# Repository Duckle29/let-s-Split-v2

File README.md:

# This repo is now an archive. Further boards and development can be found here: https://github.com/Duckle29/Vitamins-included

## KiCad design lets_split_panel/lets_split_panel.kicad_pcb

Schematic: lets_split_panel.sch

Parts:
FID1, FID2, FID3, FID4, FID5, FID6: Fiducial; Fiducial_1mm_Dia_2mm_Outer

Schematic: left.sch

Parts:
C1, C4: 1uF; C_0603
C2, C3: 18pF; C_0603
D1, D2, D3, D4, D5, D6, D7, D8, D9, D10, D11, D12: BAV70; SOT-23
J1: Speaker; Buzzer_12x9.5RM7.6
J3: ISP; Pin_Header_Straight_2x03_Pitch2.54mm
J7: WS2812>; Pin_Header_Straight_1x01_Pitch2.54mm
JP1, JP2: I2C pullup; Solder-jumper-NO
P2: UJ2-MBH-1-SMT; USB-Mini-B-SMD
P3: >WS2812; SMD_PAD_1x03_Pitch2.54mm
P4: SJ-43514-SMT; SJ-4351X-SMT
R1, R2, R6: 4k7; R_0603
R3: 200R; R_0603
R4, R5: 22R; R_0603
SW1, SW2, SW3, SW4, SW5, SW6, SW7, SW8, SW9, SW10, SW11, SW12, SW13, SW14, SW15, SW16, SW17, SW18, SW19, SW20, SW21, SW22, SW23, SW24: Socket; Kailh-socket
U1: ATMega32U4; QFN44G-0.5-7X7MM
Y1: 16MHz; Crystal_SMD_Abracon_ABM3-2pin_5.0x3.2mm

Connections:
/Left half/D+: R5.2, U1.4 (D+)
/Left half/D-: R4.2, U1.3 (D-)
/Left half/Dd+: P2.3 (D+), R5.1
/Left half/Dd-: P2.2 (D-), R4.1
/Left half/MISO: J3.1, U1.11 ((MISO)PB3)
/Left half/MOSI: J3.4, U1.10 ((MOSI)PB2)
/Left half/SCK: J3.3, U1.9 ((SCK)PB1)
/Left half/SCL/D3: P4.3, R2.2, U1.18 (~~(INT0/SCL)PD0)
/Left half/SDA: J7.1, P4.4, R1.2, U1.19 ((INT1/SDA)PD1)
/Left half/buzz: R3.1, U1.31 (~~PC6)
/Left half/col0: SW1.1, SW7.1, SW13.1, SW19.1, U1.40 ((A1)PF1)
/Left half/col1: SW2.2, SW8.2, SW14.2, SW20.2, U1.39 ((A4)PF4)
/Left half/col2: SW3.1, SW9.1, SW15.1, SW21.1, U1.33 (PE2)
/Left half/col3: SW4.2, SW10.2, SW16.2, SW22.2, U1.30 (~~(A13)PB6)
/Left half/col4: SW5.1, SW11.1, SW17.1, SW23.1, U1.27 (~~(ADC10)PD7)
/Left half/col5: SW6.2, SW12.2, SW18.2, SW24.2, U1.26 (~~(ADC9)PD6); also elsewhere on the board
/Left half/row0: D1.3, D2.3, D3.3, U1.38 ((A5)PF5)
/Left half/row1: D4.3, D5.3, D6.3, U1.37 ((A6)PF6)
/Left half/row2: D7.3, D8.3, D9.3, U1.32 (~~PC7)
/Left half/row3: D10.3, D11.3, D12.3, U1.36 ((A7)PF7)
/Left half/wd2812-in: P3.2, U1.41 ((A0)PF0)
/Left half/~Reset: J3.5, R6.1, U1.13 (~RESET~)
GND: C1.2, C2.2, C3.2, C4.2, J1.2, J3.6, P2.5 (GND), P2.6 (shield), P3.3, P4.1, U1.5 (UGND), U1.15 (GND), U1.23 (GND), U1.35 (GND), U1.43 (GND), U1.TAB (GND); also elsewhere on the board
unnamed: C2.1, U1.17 (XTAL1), Y1.1
unnamed: C3.1, U1.16 (XTAL2), Y1.2
unnamed: C4.1, U1.6 (UCap)
unnamed: D1.1, SW1.2
unnamed: D1.2, SW2.1
unnamed: D2.1, SW3.2
unnamed: D2.2, SW4.1
unnamed: D3.1, SW5.2
unnamed: D3.2, SW6.1
unnamed: D4.1, SW7.2
unnamed: D4.2, SW8.1
unnamed: D5.1, SW9.2
unnamed: D5.2, SW10.1
unnamed: D6.1, SW11.2
unnamed: D6.2, SW12.1
unnamed: D7.1, SW13.2
unnamed: D7.2, SW14.1
unnamed: D8.1, SW15.2
unnamed: D8.2, SW16.1
unnamed: D9.1, SW17.2
unnamed: D9.2, SW18.1
unnamed: D10.1, SW19.2
unnamed: D10.2, SW20.1
unnamed: D11.1, SW21.2
unnamed: D11.2, SW22.1
unnamed: D12.1, SW23.2
unnamed 74: D12.2, SW24.1; also elsewhere on the board
unnamed: J1.1, R3.2
unnamed: JP1.2, R1.1
unnamed: JP2.2, R2.1
VBUS: C1.1, J3.2, JP1.1, JP2.1, P2.1 (VCC), P3.1, P4.2, R6.2, U1.2 (UVCC), U1.7 (VBUS), U1.14 (VCC), U1.24 (AVCC), U1.34 (VCC), U1.44 (AVCC); also elsewhere on the board

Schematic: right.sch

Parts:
C5, C8: 1uF; C_0603
C6, C7: 18pF; C_0603
D13, D14, D15, D16, D17, D18, D19, D20, D21, D22, D23, D24: BAV70; SOT-23
J5: Speaker; Buzzer_12x9.5RM7.6
J6: ISP; Pin_Header_Straight_2x03_Pitch2.54mm
J8: WS2812>; Pin_Header_Straight_1x01_Pitch2.54mm
P5: UJ2-MBH-1-SMT; USB-Mini-B-SMD
P6: >WS2812; SMD_PAD_1x03_Pitch2.54mm
P8: SJ-43514-SMT; SJ-4351X-SMT
R7, R8: 22R; R_0603
R9: 4k7; R_0603
R10: 200R; R_0603
SW25, SW26, SW27, SW28, SW29, SW30, SW31, SW32, SW33, SW34, SW35, SW36, SW37, SW38, SW39, SW40, SW41, SW42, SW43, SW44, SW45, SW46, SW47, SW48: Socket; Kailh-socket
U2: ATMega32U4; QFN44G-0.5-7X7MM
Y2: 16MHz; Crystal_SMD_Abracon_ABM3-2pin_5.0x3.2mm

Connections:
/Right half/D+: R8.2, U2.4 (D+)
/Right half/D-: R7.2, U2.3 (D-)
/Right half/Dd+: P5.3 (D+), R8.1
/Right half/Dd-: P5.2 (D-), R7.1
/Right half/MISO: J6.1, U2.11 ((MISO)PB3)
/Right half/MOSI: J6.4, U2.10 ((MOSI)PB2)
/Right half/SCK: J6.3, U2.9 ((SCK)PB1)
/Right half/SCL/D3: P8.3, U2.18 (~~(INT0/SCL)PD0)
/Right half/SDA: J8.1, P8.4, U2.19 ((INT1/SDA)PD1)
/Right half/WD2812-in: P6.2, U2.41 ((A0)PF0)
/Right half/buzz: R10.1, U2.31 (~~PC6)
/Right half/col0: SW25.1, SW31.1, SW37.1, SW43.1, U2.40 ((A1)PF1); also elsewhere on the board
/Right half/col1: SW26.2, SW32.2, SW38.2, SW44.2, U2.39 ((A4)PF4)
/Right half/col2: SW27.1, SW33.1, SW39.1, SW45.1, U2.33 (PE2)
/Right half/col3: SW28.2, SW34.2, SW40.2, SW46.2, U2.30 (~~(A13)PB6)
/Right half/col4: SW29.1, SW35.1, SW41.1, SW47.1, U2.27 (~~(ADC10)PD7)
/Right half/col5: SW30.2, SW36.2, SW42.2, SW48.2, U2.26 (~~(ADC9)PD6)
/Right half/row0: D13.3, D14.3, D15.3, U2.38 ((A5)PF5)
/Right half/row1: D16.3, D17.3, D18.3, U2.37 ((A6)PF6)
/Right half/row2: D19.3, D20.3, D21.3, U2.32 (~~PC7)
/Right half/row3: D22.3, D23.3, D24.3, U2.36 ((A7)PF7)
/Right half/~RESET: J6.5, R9.1, U2.13 (~RESET~)
GND: C5.2, C6.2, C7.2, C8.2, J5.2, J6.6, P5.5 (GND), P5.6 (shield), P6.3, P8.1, U2.5 (UGND), U2.15 (GND), U2.23 (GND), U2.35 (GND), U2.43 (GND), U2.TAB (GND); also elsewhere on the board
unnamed: C6.1, U2.17 (XTAL1), Y2.1
unnamed: C7.1, U2.16 (XTAL2), Y2.2
unnamed: C8.1, U2.6 (UCap)
unnamed: D13.1, SW25.2
unnamed: D13.2, SW26.1
unnamed: D14.1, SW27.2
unnamed: D14.2, SW28.1
unnamed: D15.1, SW29.2
unnamed: D15.2, SW30.1
unnamed: D16.1, SW31.2
unnamed: D16.2, SW32.1
unnamed: D17.1, SW33.2
unnamed: D17.2, SW34.1
unnamed: D18.1, SW35.2
unnamed: D18.2, SW36.1
unnamed: D19.1, SW37.2
unnamed: D19.2, SW38.1
unnamed: D20.1, SW39.2
unnamed: D20.2, SW40.1
unnamed: D21.1, SW41.2
unnamed: D21.2, SW42.1
unnamed 93: D22.1, SW43.2; also elsewhere on the board
unnamed: D22.2, SW44.1
unnamed: D23.1, SW45.2
unnamed: D23.2, SW46.1
unnamed: D24.1, SW47.2
unnamed: D24.2, SW48.1
unnamed: J5.1, R10.2
VBUS: C5.1, J6.2, P5.1 (VCC), P6.1, P8.2, R9.2, U2.2 (UVCC), U2.7 (VBUS), U2.14 (VCC), U2.24 (AVCC), U2.34 (VCC), U2.44 (AVCC); also elsewhere on the board

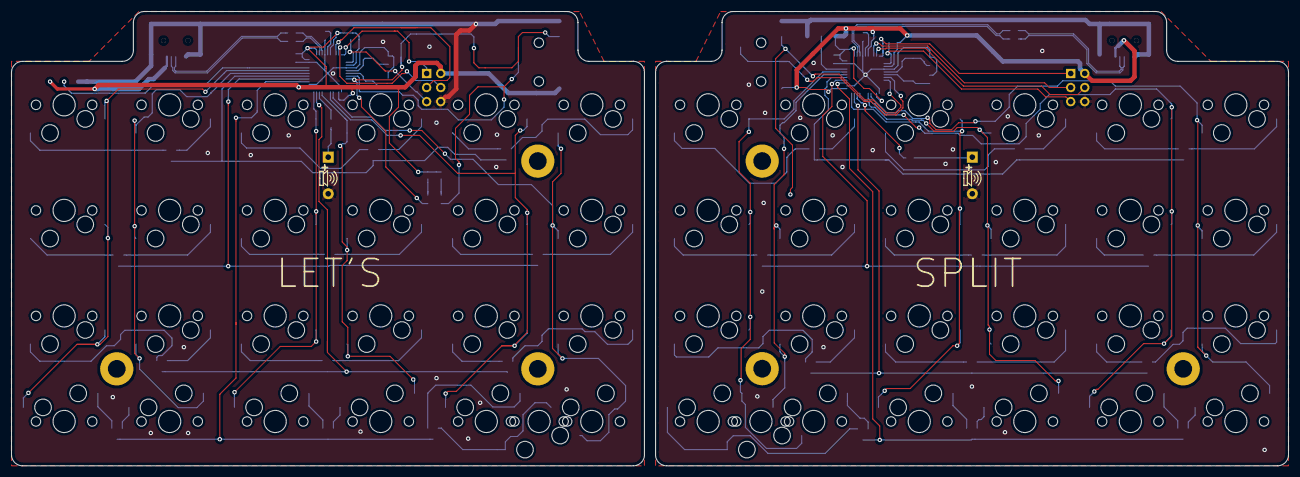
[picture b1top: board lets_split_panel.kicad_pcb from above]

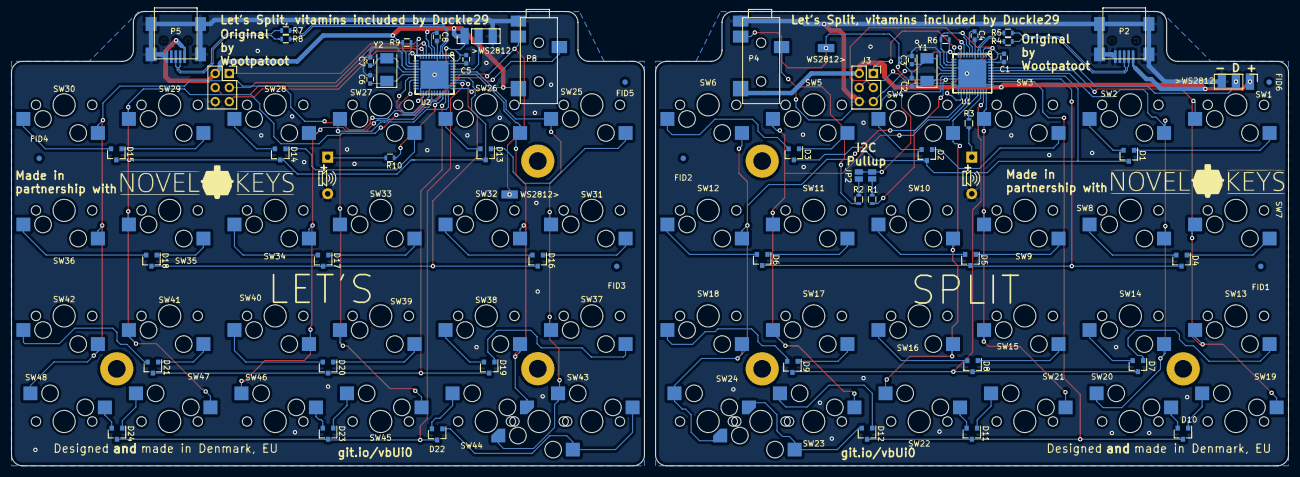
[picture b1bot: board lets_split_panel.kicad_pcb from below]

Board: 2 copper layers, 230.5 x 82.0 mm, 116 parts (64 on the bottom side), 104 nets.

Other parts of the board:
SW24#2, SW43#2: Socket; Kailh-socket

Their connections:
/Left half/col5: SW24#2.2; also elsewhere on the board
/Right half/col0: SW43#2.1; also elsewhere on the board
unnamed 74: SW24#2.1; also elsewhere on the board
unnamed 93: SW43#2.2; also elsewhere on the board

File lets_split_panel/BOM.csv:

"Id";"Designator";"Package";"Quantity";"Designation";"Supplier and ref";
1;"G***,G***";"kiwi";2;"LOGO";;;
2;"FID6,FID4,FID5,FID3,FID2,FID1";"Fiducial_1mm_Dia_2mm_Outer";6;"Fiducial";;;
3;"P5,P2";"USB-Mini-B-SMD";2;"UJ2-MBH-1-SMT";;;
4;"D21,D16,D23,D14,D20,D22,D19,D24,D17,D15,D13,D18,D2,D8,D6,D12,D3,D7,D10,D4,D9,D11,D5,D1";"SOT-23";24;"BAV70";;;
5;"R7,R8,R5,R4";"R_0603";4;"22R";;;
6;"SW40,SW36,SW41,SW43,SW44,SW42,SW45,SW43,SW35,SW28,SW34,SW48,SW47,SW33,SW39,SW32,SW26,SW29,SW46,SW30,SW38,SW27,SW31,SW25,SW37,SW19,SW12,SW21,SW23,SW24,SW24,SW6,SW15,SW4,SW5,SW13,SW20,SW1,SW22,SW16,SW17,SW8,SW10,SW11,SW7,SW9,SW18,SW2,SW14,SW3";"Kailh-socket";50;"Socket";;;
7;"Y2,Y1";"Crystal_SMD_Abracon_ABM3-2pin_5.0x3.2mm";2;"16MHz";;;
8;"P6,P3";"SMD_PAD_1x03_Pitch2.54mm";2;">WS2812";;;
9;"P8,P4";"SJ-4351X-SMT";2;"SJ-43514-SMT";;;
10;"J8,J7";"Pin_Header_Straight_1x01_Pitch2.54mm";2;"WS2812>";;;
11;"C6,C7,C2,C3";"C_0603";4;"18pF";;;
12;"C5,C8,C1,C4";"C_0603";4;"1uF";;;
13;"REF**,REF**,REF**,REF**,REF**,REF**";"1pin";6;"1pin";;;
14;"U2,U1";"QFN44G-0.5-7X7MM";2;"ATMega32U4";;;
15;"R10,R3";"R_0603";2;"200R";;;
16;"R9,R1,R2,R6";"R_0603";4;"4k7";;;
17;"J6,J3";"Pin_Header_Straight_2x03_Pitch2.54mm";2;"ISP";;;
18;"J5,J1";"Buzzer_12x9.5RM7.6";2;"Speaker";;;
19;"G***,G***";"NovelKeys";2;"LOGO";;;
20;"JP1,JP2";"Solder-jumper-NO";2;"I2C pullup";;;

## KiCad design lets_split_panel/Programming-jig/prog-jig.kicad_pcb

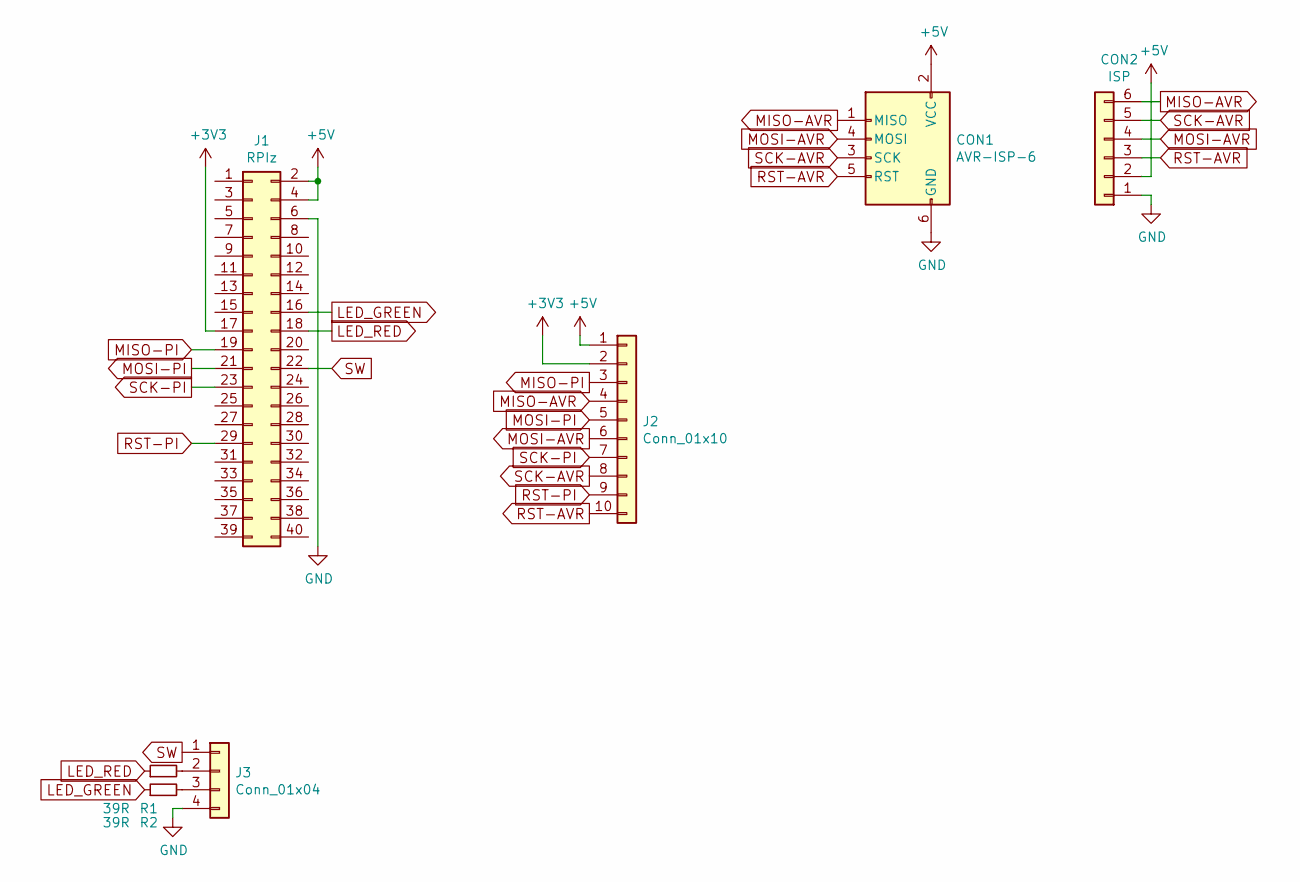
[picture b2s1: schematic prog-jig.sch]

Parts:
CON1: AVR-ISP-6; Pin_Header_Straight_2x03_Pitch2.54mm
CON2: ISP; Pin_Header_Straight_1x06_Pitch2.54mm
J1: RPIz; Socket_Strip_Straight_2x20_Pitch2.54mm
J2: Conn_01x10; Pin_Header_Straight_1x10_Pitch2.54mm
J3: Conn_01x04; Pin_Header_Angled_1x04_Pitch2.54mm
R1, R2: 39R; R_0603_HandSoldering

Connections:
+3V3: J1.17, J2.2
+5V: CON1.2 (VCC), CON2.2, J1.2, J1.4, J2.1
GND: CON1.6 (GND), CON2.1, J1.6, J3.4
LED_GREEN: J1.16, R2.1
LED_RED: J1.18, R1.1
MISO-AVR: CON1.1 (MISO), CON2.6, J2.4
MISO-PI: J1.19, J2.3
MOSI-AVR: CON1.4 (MOSI), CON2.4, J2.6
MOSI-PI: J1.21, J2.5
unnamed: J3.2, R1.2
unnamed: J3.3, R2.2
RST-AVR: CON1.5 (RST), CON2.3, J2.10
RST-PI: J1.29, J2.9
SCK-AVR: CON1.3 (SCK), CON2.5, J2.8
SCK-PI: J1.23, J2.7
SW: J1.22, J3.1

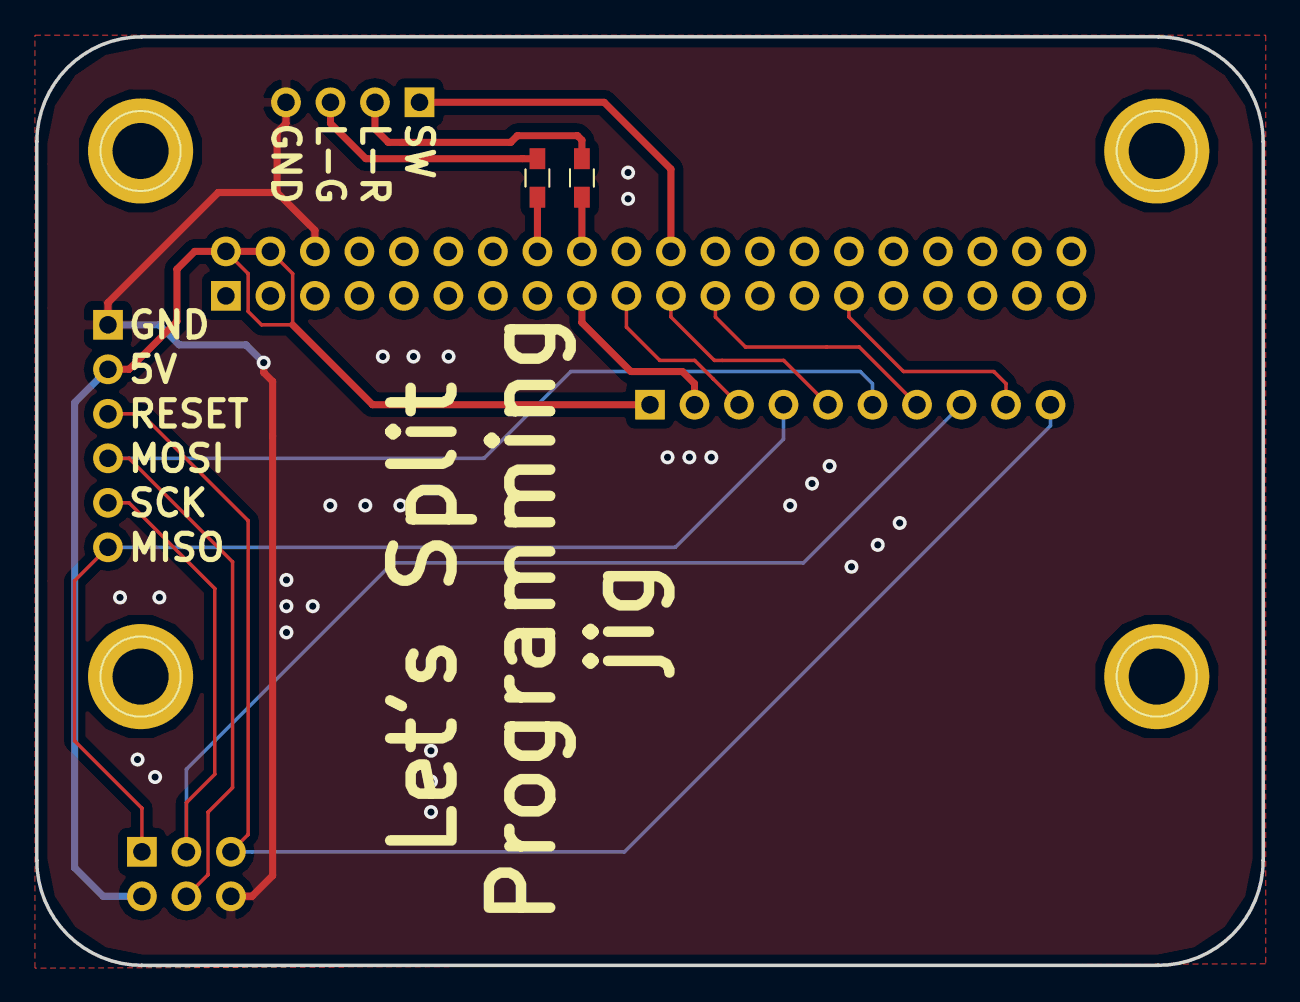
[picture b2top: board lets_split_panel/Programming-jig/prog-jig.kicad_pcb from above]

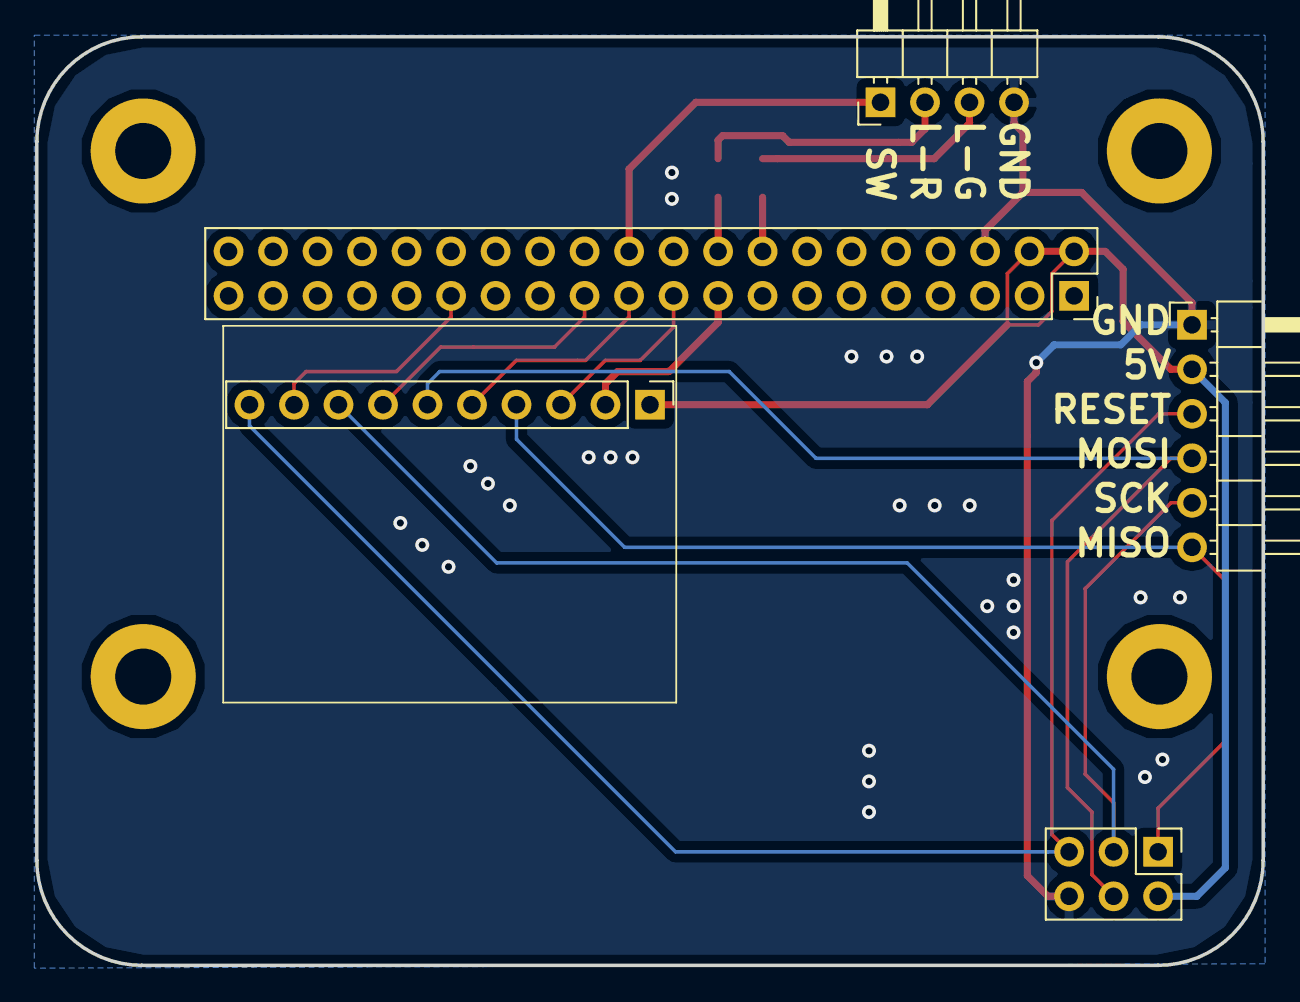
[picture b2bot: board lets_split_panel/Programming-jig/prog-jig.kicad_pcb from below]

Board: 2 copper layers, 70.0 x 53.0 mm, 7 parts (5 on the bottom side), 16 nets.

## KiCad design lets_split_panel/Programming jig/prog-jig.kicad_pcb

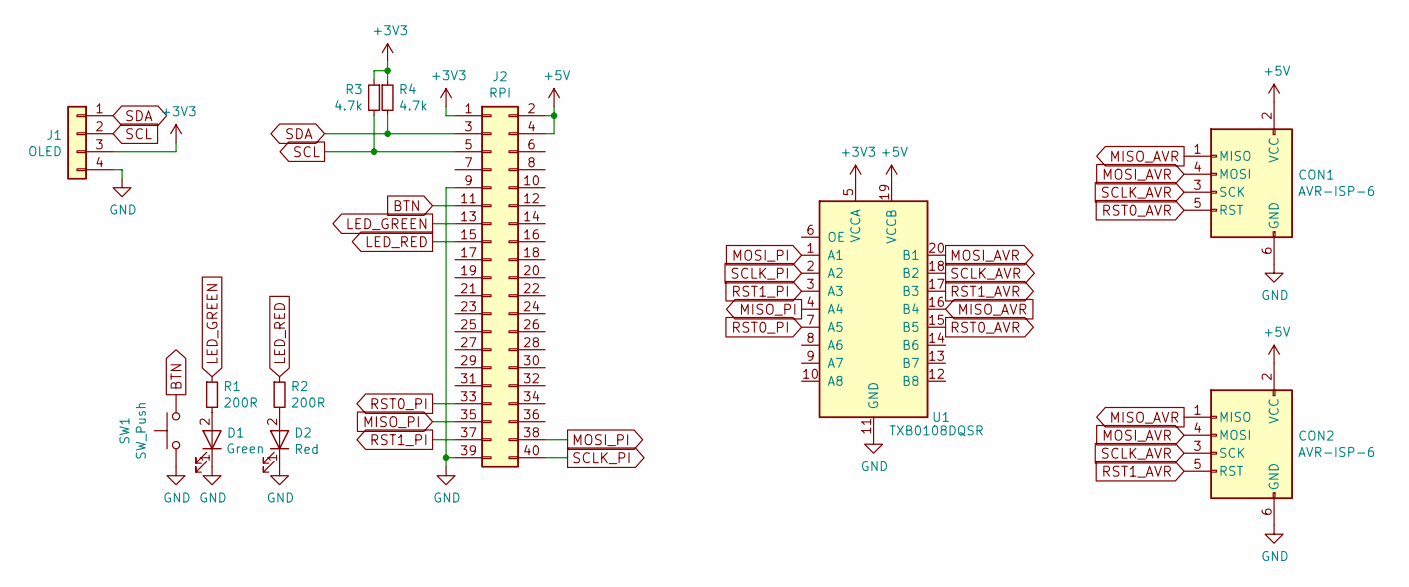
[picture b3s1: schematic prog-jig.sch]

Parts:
CON1, CON2: AVR-ISP-6; Pin_Header_Straight_2x03_Pitch2.54mm
D1: Green; LED_D5.0mm
D2: Red; LED_D5.0mm
J1: OLED; Pin_Header_Straight_1x04_Pitch2.54mm
J2: RPI; Pin_Header_Straight_2x20_Pitch2.54mm
R1, R2: 200R; R_Axial_DIN0207_L6.3mm_D2.5mm_P15.24mm_Horizontal
R3, R4: 4.7k; R_Axial_DIN0204_L3.6mm_D1.6mm_P7.62mm_Horizontal
SW1: SW_Push; SW_PUSH_6mm
U1: TXB0108DQSR; Adafruit-TXB0108

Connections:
+3V3: J1.3, J2.1, R3.1, R4.1, U1.5 (VCCA)
+5V: CON1.2 (VCC), CON2.2 (VCC), J2.2, J2.4, U1.19 (VCCB)
BTN: J2.11, SW1.2
GND: CON1.6 (GND), CON2.6 (GND), D1.1 (K), D2.1 (K), J1.4, J2.9, J2.39, SW1.1, U1.11 (GND)
LED_GREEN: J2.13, R1.1
LED_RED: J2.15, R2.1
MISO_AVR: CON1.1 (MISO), CON2.1 (MISO), U1.16 (B4)
MISO_PI: J2.35, U1.4 (A4)
MOSI_AVR: CON1.4 (MOSI), CON2.4 (MOSI), U1.20 (B1)
MOSI_PI: J2.38, U1.1 (A1)
unnamed: D1.2 (A), R1.2
unnamed: D2.2 (A), R2.2
RST0_AVR: CON1.5 (RST), U1.15 (B5)
RST0_PI: J2.33, U1.7 (A5)
RST1_AVR: CON2.5 (RST), U1.17 (B3)
RST1_PI: J2.37, U1.3 (A3)
SCL: J1.2, J2.5, R3.2
SCLK_AVR: CON1.3 (SCK), CON2.3 (SCK), U1.18 (B2)
SCLK_PI: J2.40, U1.2 (A2)
SDA: J1.1, J2.3, R4.2

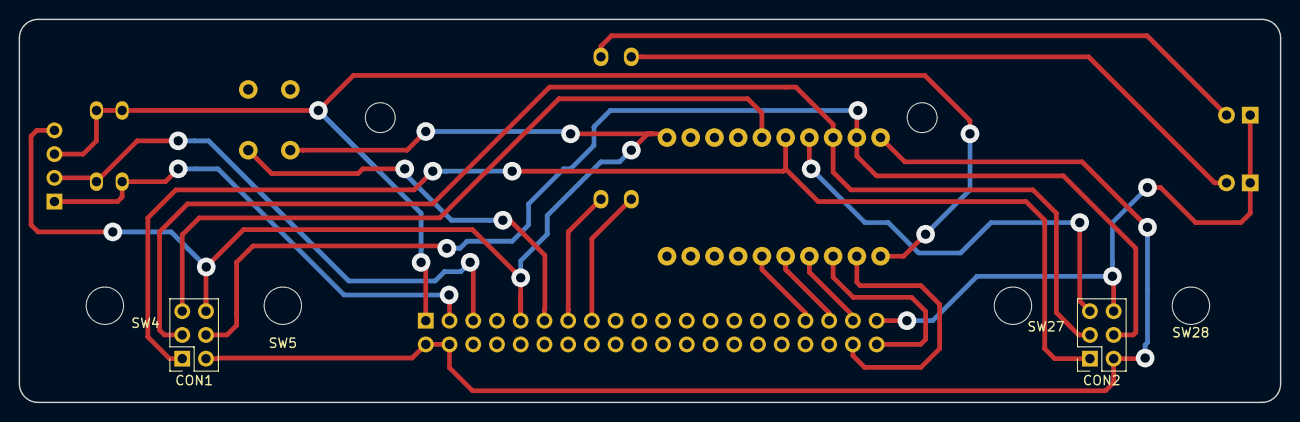
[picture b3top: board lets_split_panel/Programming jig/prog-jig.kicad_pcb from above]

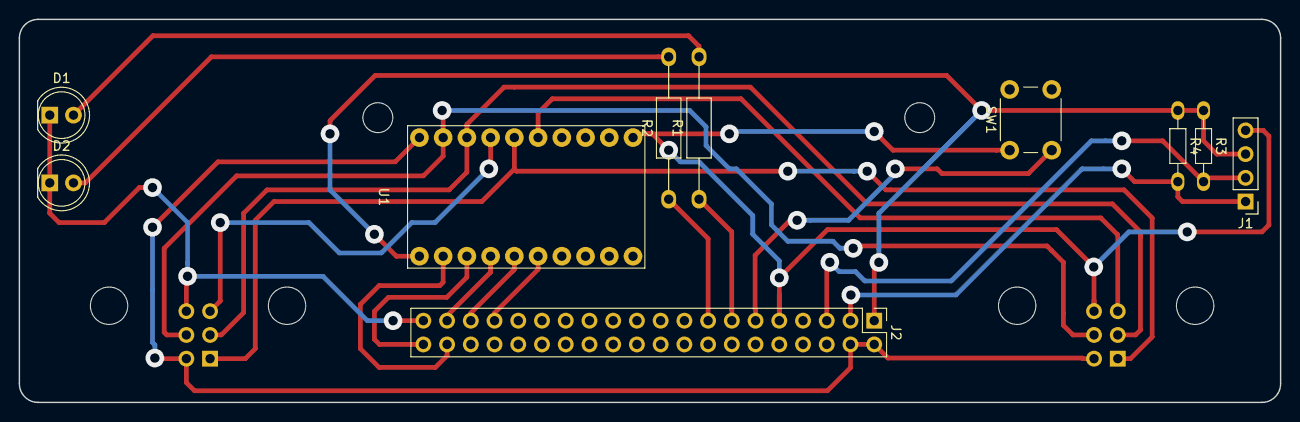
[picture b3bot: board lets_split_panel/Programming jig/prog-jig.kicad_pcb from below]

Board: 2 copper layers, 135.0 x 41.0 mm, 16 parts (16 on the bottom side), 20 nets.

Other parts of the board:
SW4, SW5, SW27, SW28: Socket; Kailh-socket

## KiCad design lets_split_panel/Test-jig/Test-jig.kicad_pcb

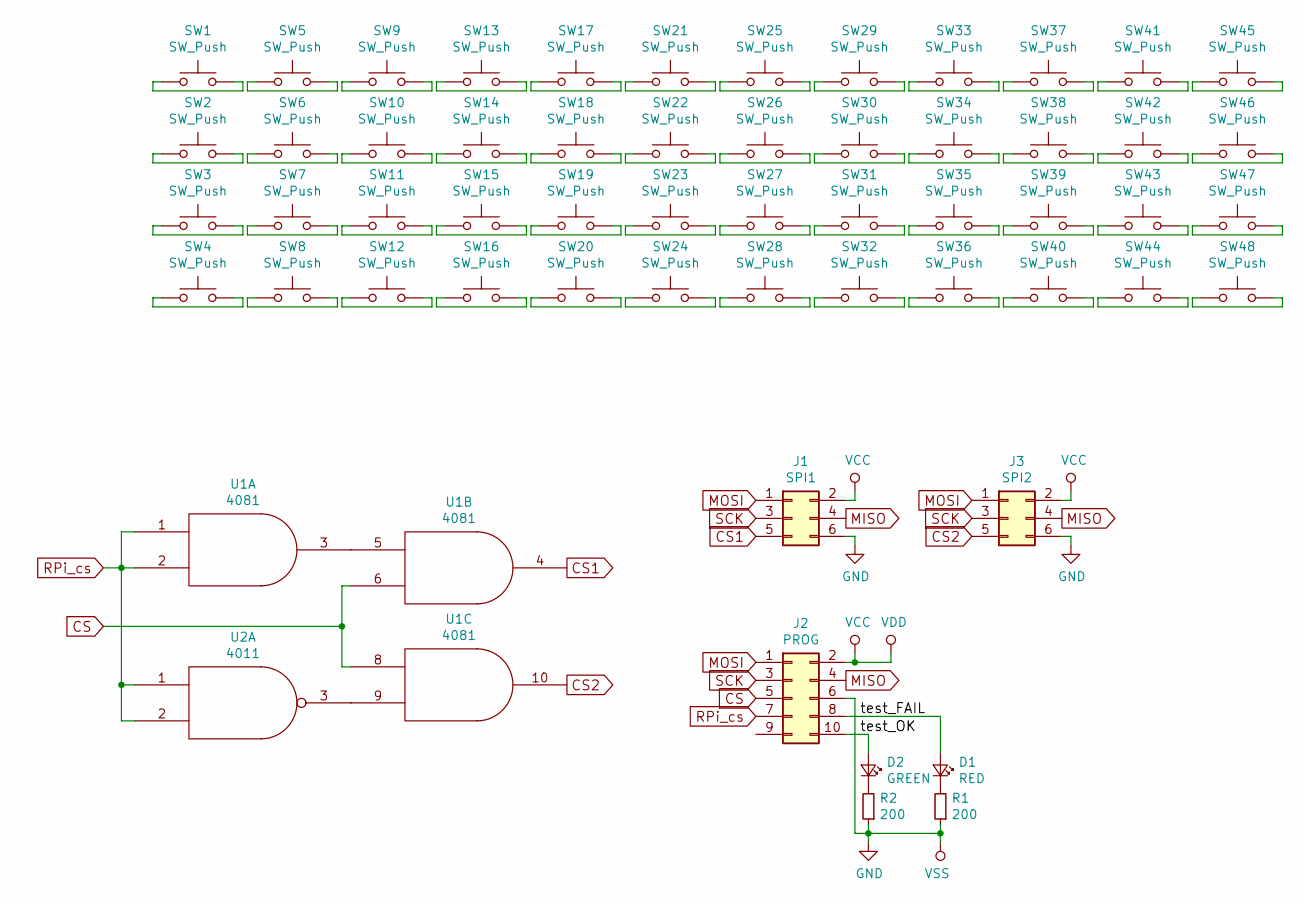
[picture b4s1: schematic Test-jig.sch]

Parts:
D1: RED; LED_D5.0mm
D2: GREEN; LED_D5.0mm
J1: SPI1; Pin_Header_Straight_2x03_Pitch2.54mm
J2: PROG; Pin_Header_Straight_2x05_Pitch2.54mm
J3: SPI2; Pin_Header_Straight_2x03_Pitch2.54mm
R1, R2: 200; R_0603_HandSoldering
SW1, SW2, SW3, SW4, SW5, SW6, SW7, SW8, SW9, SW10, SW11, SW12, SW13, SW14, SW15, SW16, SW17, SW18, SW19, SW20, SW21, SW22, SW23, SW24, SW25, SW26, SW27, SW28, SW29, SW30, SW31, SW32, SW33, SW34, SW35, SW36, SW37, SW38, SW39, SW40, SW41, SW42, SW43, SW44, SW45, SW46, SW47, SW48: SW_Push; Kailh-socket-P50-Q1-probe
U1: 4081; DIP-14_W7.62mm
U2: 4011; DIP-14_W7.62mm

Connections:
/test_FAIL: D1.2 (A), J2.8
/test_OK: D2.2 (A), J2.10
CS: J2.5, U1.6, U1.8
CS1: J1.5, U1.4
CS2: J3.5, U1.10
GND: J1.6, J2.6, J3.6, R1.1, R2.1, U1.7 (VSS), U2.7 (VSS)
MISO: J1.4, J2.4, J3.4
MOSI: J1.1, J2.1, J3.1
unnamed: D1.1 (K), R1.2
unnamed: D2.1 (K), R2.2
unnamed: SW1.1, SW1.2
unnamed: SW2.1, SW2.2
unnamed: SW3.1, SW3.2
unnamed: SW4.1, SW4.2
unnamed: SW5.1, SW5.2
unnamed: SW6.1, SW6.2
unnamed: SW7.1, SW7.2
unnamed: SW8.1, SW8.2
unnamed: SW9.1, SW9.2
unnamed: SW10.1, SW10.2
unnamed: SW11.1, SW11.2
unnamed: SW12.1, SW12.2
unnamed: SW13.1, SW13.2
unnamed: SW14.1, SW14.2
unnamed: SW15.1, SW15.2
unnamed: SW16.1, SW16.2
unnamed: SW17.1, SW17.2
unnamed: SW18.1, SW18.2
unnamed: SW19.1, SW19.2
unnamed: SW20.1, SW20.2
unnamed: SW21.1, SW21.2
unnamed: SW22.1, SW22.2
unnamed: SW23.1, SW23.2
unnamed: SW24.1, SW24.2
unnamed: SW25.1, SW25.2
unnamed: SW26.1, SW26.2
unnamed: SW27.1, SW27.2
unnamed: SW28.1, SW28.2
unnamed: SW29.1, SW29.2
unnamed: SW30.1, SW30.2
unnamed: SW31.1, SW31.2
unnamed: SW32.1, SW32.2
unnamed: SW33.1, SW33.2
unnamed: SW34.1, SW34.2
unnamed: SW35.1, SW35.2
unnamed: SW36.1, SW36.2
unnamed: SW37.1, SW37.2
unnamed: SW38.1, SW38.2
unnamed: SW39.1, SW39.2
unnamed: SW40.1, SW40.2
unnamed: SW41.1, SW41.2
unnamed: SW42.1, SW42.2
unnamed: SW43.1, SW43.2
unnamed: SW44.1, SW44.2
unnamed: SW45.1, SW45.2
unnamed: SW46.1, SW46.2
unnamed: SW47.1, SW47.2
unnamed: SW48.1, SW48.2
unnamed: U1.3, U1.5
unnamed: U1.9, U2.3
RPi_cs: J2.7, U1.1, U1.2, U2.1, U2.2
SCK: J1.3, J2.3, J3.3
VCC: J1.2, J2.2, J3.2, U1.14 (VDD), U2.14 (VDD)

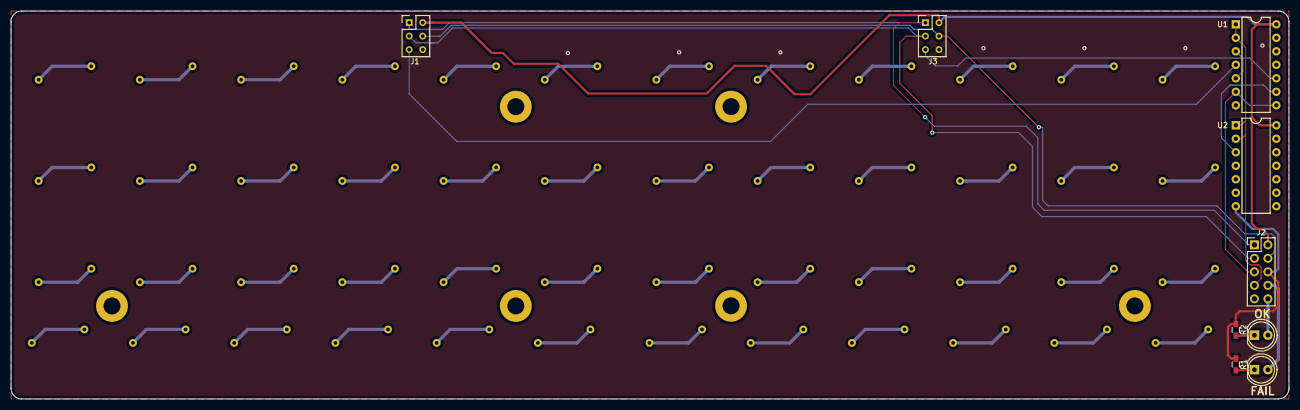
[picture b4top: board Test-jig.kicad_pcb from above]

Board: 2 copper layers, 240.5 x 73.0 mm, 57 parts (0 on the bottom side), 63 nets.

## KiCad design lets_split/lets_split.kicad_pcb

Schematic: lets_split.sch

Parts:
C1, C4: 1uF; C0603
C2, C3: 8pF; C0402
D1, D2, D3, D4, D5, D6, D7, D8, D9, D10, D11, D12, D13, D14, D15, D16, D17, D18, D19, D20, D21, D22, D23, D24: D; SOD-123
J1: Speaker; Buzzer_12x9.5RM7.6
J2: RST; Pin_Header_Straight_1x02_Pitch2.54mm
J3: ISP; J-link-needle-6pin
JP1, JP2: I2C pullup; Solder-jumper-NO
P1: WS2812>; SMD_PAD_1x03_Pitch2.54mm
P2: USB_OTG; USB-Mini-B-SMD
P3: >WS2812; SMD_PAD_1x03_Pitch2.54mm
P4: Conn_01x04; SJ-4351X-SMT
R1, R2, R6: 4k7; R_0603_HandSoldering
R3: 200; R_0603_HandSoldering
R4, R5: 22R; R_0603_HandSoldering
SW1, SW2, SW3, SW4, SW5, SW6, SW7, SW8, SW9, SW10, SW11, SW12, SW13, SW14, SW15, SW16, SW17, SW18, SW19, SW20, SW21, SW22, SW23, SW24: MXALPS; Kailh-socket
U1: ATMega32U4; QFN44G-0.5-7X7MM
Y1: Crystal; X2-SMD-5.0X3.2X1.3MM

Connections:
/D+: R5.2, U1.4 (D+)
/D-: R4.2, U1.3 (D-)
/MISO: J3.1, U1.11 ((MISO)PB3)
/MOSI: J3.4, U1.10 ((MOSI)PB2)
/SCK: J3.3, U1.9 ((SCK)PB1)
/SCL/D3: P4.3, R2.2, U1.18 (~~(INT0/SCL)PD0)
/SDA: P1.2, P4.4, R1.2, U1.19 ((INT1/SDA)PD1)
/WD2812-in: P3.2, U1.41 ((A0)PF0)
/buzz: R3.1, U1.31 (~~PC6)
/col0: SW1.1, SW7.1, SW13.1, SW19.1, U1.40 ((A1)PF1)
/col1: SW2.1, SW8.1, SW14.1, SW20.1, U1.39 ((A4)PF4)
/col2: SW3.1, SW9.1, SW15.1, SW21.1, U1.33 (PE2)
/col3: SW4.1, SW10.1, SW16.1, SW22.1, U1.30 (~~(A13)PB6)
/col4: SW5.1, SW11.1, SW17.1, SW23.1, U1.27 (~~(ADC10)PD7)
/col5: SW6.1, SW12.1, SW18.1, SW24.1, U1.26 (~~(ADC9)PD6)
/row0: D1.1 (K), D5.1 (K), D9.1 (K), D13.1 (K), D17.1 (K), D21.1 (K), U1.38 ((A5)PF5)
/row1: D2.1 (K), D6.1 (K), D10.1 (K), D14.1 (K), D18.1 (K), D22.1 (K), U1.37 ((A6)PF6)
/row2: D3.1 (K), D7.1 (K), D11.1 (K), D15.1 (K), D19.1 (K), D23.1 (K), U1.32 (~~PC7)
/row3: D4.1 (K), D8.1 (K), D12.1 (K), D16.1 (K), D20.1 (K), D24.1 (K), U1.36 ((A7)PF7)
/~RESET: J2.2, J3.5, R6.1, U1.13 (~RESET~)
GND: C1.2, C2.2, C3.2, C4.2, J1.2, J2.1, J3.6, P1.3, P2.5 (GND), P2.6 (shield), P3.3, P4.1, U1.5 (UGND), U1.15 (GND), U1.23 (GND), U1.35 (GND), U1.43 (GND), U1.TAB (GND)
unnamed: C2.1, U1.17 (XTAL1), Y1.1
unnamed: C3.1, U1.16 (XTAL2), Y1.2
unnamed: C4.1, U1.6 (UCap)
unnamed: D1.2 (A), SW1.2
unnamed: D2.2 (A), SW7.2
unnamed: D3.2 (A), SW13.2
unnamed: D4.2 (A), SW19.2
unnamed: D5.2 (A), SW2.2
unnamed: D6.2 (A), SW8.2
unnamed: D7.2 (A), SW14.2
unnamed: D8.2 (A), SW20.2
unnamed: D9.2 (A), SW3.2
unnamed: D10.2 (A), SW9.2
unnamed: D11.2 (A), SW15.2
unnamed: D12.2 (A), SW21.2
unnamed: D13.2 (A), SW4.2
unnamed: D14.2 (A), SW10.2
unnamed: D15.2 (A), SW16.2
unnamed: D16.2 (A), SW22.2
unnamed: D17.2 (A), SW5.2
unnamed: D18.2 (A), SW11.2
unnamed: D19.2 (A), SW17.2
unnamed: D20.2 (A), SW23.2
unnamed: D21.2 (A), SW6.2
unnamed: D22.2 (A), SW12.2
unnamed: D23.2 (A), SW18.2
unnamed: D24.2 (A), SW24.2
unnamed: J1.1, R3.2
unnamed: JP1.2, R1.1
unnamed: JP2.2, R2.1
unnamed: P2.2 (D-), R4.1
unnamed: P2.3 (D+), R5.1
VBUS: C1.1, J3.2, JP1.1, JP2.1, P1.1, P2.1 (VCC), P3.1, P4.2, R6.2, U1.2 (UVCC), U1.7 (VBUS), U1.14 (VCC), U1.24 (AVCC), U1.34 (VCC), U1.44 (AVCC)

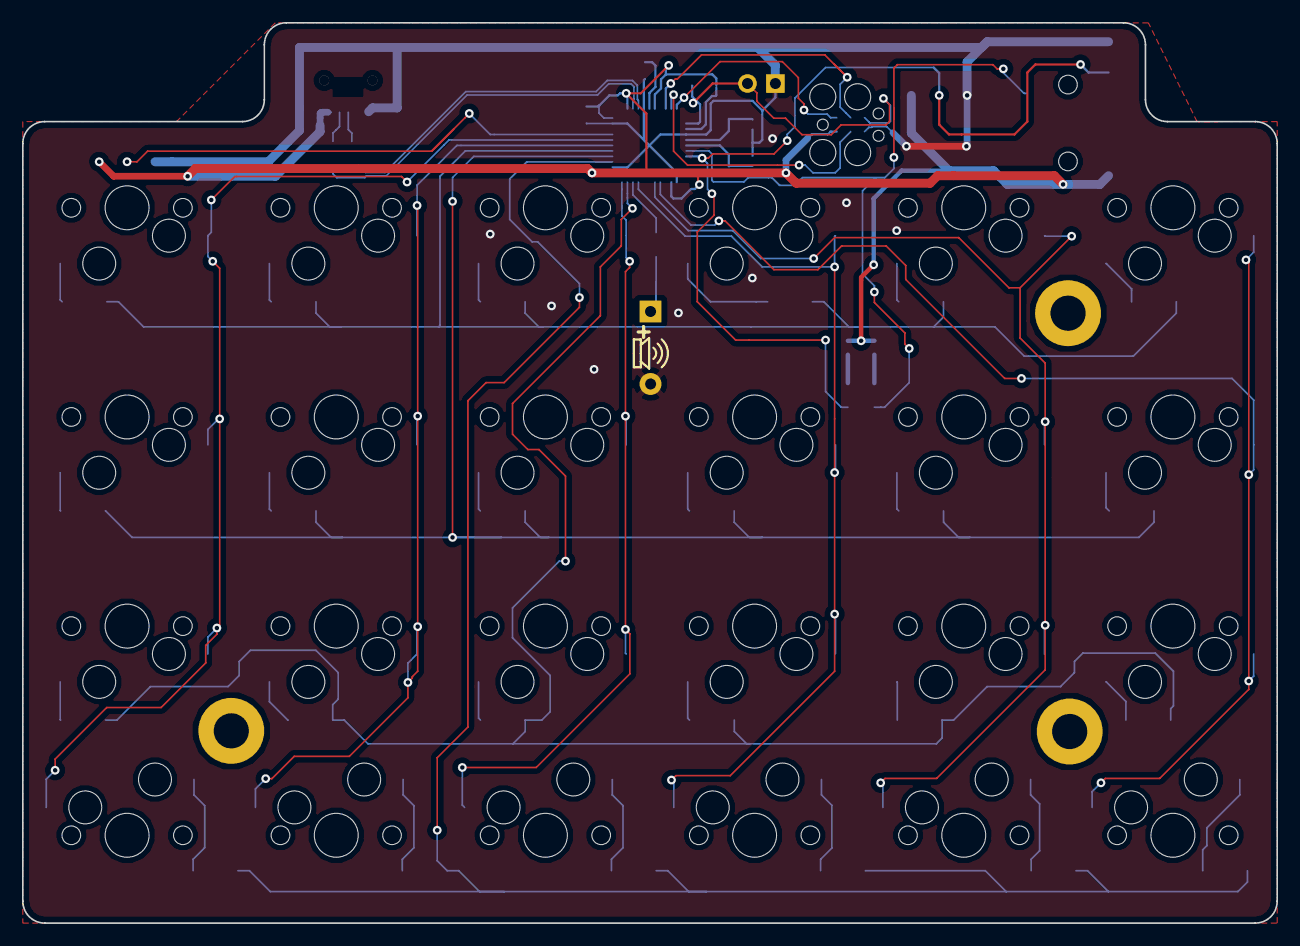
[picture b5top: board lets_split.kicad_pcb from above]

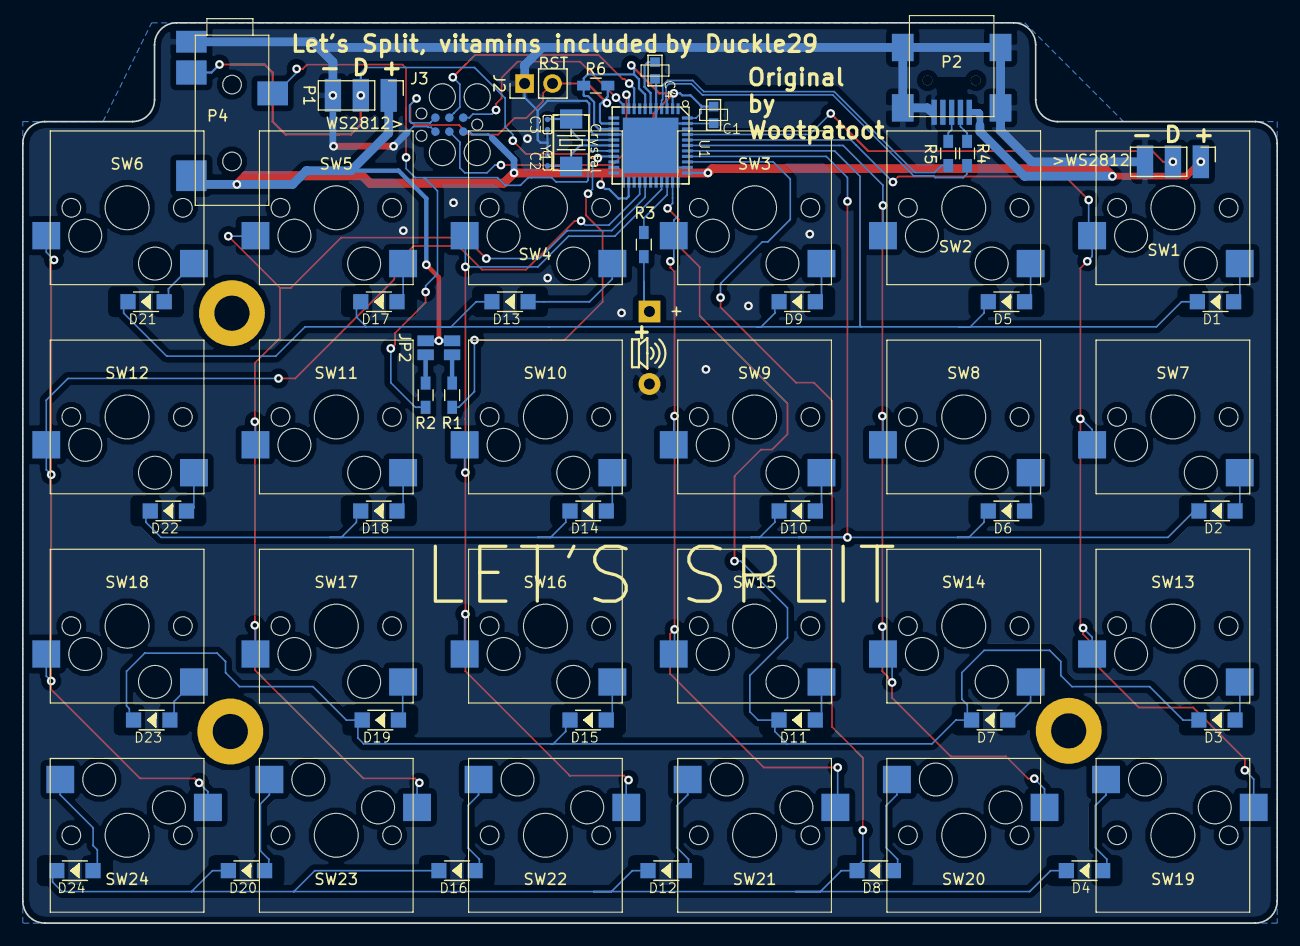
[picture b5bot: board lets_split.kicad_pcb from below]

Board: 2 copper layers, 114.2 x 82.0 mm, 69 parts (45 on the bottom side), 54 nets.

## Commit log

2017-10-10 Changed to use kailh sockets, start of branch
2017-10-10 Deleted .bak file
2017-10-10 First layout, need to add MCU
2017-10-10 Finished desing
2017-10-10 Added zipped gerber and renders
2017-10-10 Removed old gerbers
2017-10-10 flipped TRRS connector the the back for both boards
2017-10-10 Moved panel files into subfolder
2017-10-10 V3 version, with mini usb added
2017-10-10 parking V3 here
2017-10-10 Finished and panelized V3
2017-10-10 Corrected micro USB to mini
2017-10-10 Added images to readme
2017-10-12 Changed to actually aquireable TRRS connector
2017-10-12 Actually saved PCB to new TRRS socket
2017-10-12 Increased powertraces thickness to TRRS socket
2017-10-12 Panelized design with new connector
2017-10-12 Finished up lettering on the panel
2017-10-14 Added SVG of schematic
2017-10-14 Made image a link to schematic
2017-10-17 Switched to using diode footprints with actual silk screen, and moved dioes away from socket pads
2017-10-17 Moved silkscreen around a bit
2017-10-17 Fixing merge stuff
2017-10-17 Revert "Fixing merge stuff"
    reverts the "fix" as it removed things I'd forgotten I'd added
2017-10-17 Routed board with reversible socket footprint, and mirrored connectors
2017-10-17 Added images of reversible version
2017-10-17 Fixed link to bottom image
2017-10-17 Updated schematic svg
2017-10-17 Changed readme to use relative links
2017-10-17 Updated absolute link to svg, as relatives don't work propperly for that
2017-10-17 Removed the whitespace from the schematic svg
2017-10-17 Added speaker output to the board
2017-10-17 Added gerbers
2017-10-17 Connected speaker to correct pin
2017-10-17 Fixed some stupid mistakes (traces over holes)
2017-10-17 Good night
2017-10-17 Good night I said
2017-10-18 Before adding cherrymx 3D model
2017-10-18 Added some 3D models and new renderse
2017-10-18 Forcing github to update images
2017-10-18 The cache is strong with this one
2017-10-19 Changed 3D file path
2017-10-19 Going home
2017-10-22 Re-poured copper
2017-10-23 Did a few small changes to routing
2017-10-23 Fixed a broken gnd path
2017-10-25 Added speaker symbol
2017-10-26 Changed footpring designations for possible PCBA in the future
2017-11-14 Moved TRRS connector to clear switches
2017-11-15 Changed .gitignore to ignore step files till they're ready
2017-11-15 First commit for mcu version
2017-11-16 Vitamins included "done"
2017-11-16 I love git. Saved PCB file, started panel work
2017-11-16 Finished panel
2017-11-16 Renamed images because aparrently they were 404 on github
2017-11-16 added topside
2017-11-16 Renamed images
2017-11-19 Made routed panel
2017-11-20 DONT MERGE!
2017-11-22 Added test jig for panel
2017-11-23 Changed to use SOT-23 dual diodes for cost
2017-11-23 Added 3D models
2017-11-23 Added option for 2U spacebars
2017-11-28 made sure USB datalines had gnd under them
2017-11-28 Re-rendered images
2017-11-29 Added fancy :)
2017-12-05 Finished programming jig
2017-12-05 Removed Programming-jig and test jig
2017-12-07 updated gerbers
2017-12-07 Seperated gerbers on request from board house
2017-12-19 Added PnP files and split gerbers
2018-01-11 Added kiwi
2018-01-14 Added BOM
